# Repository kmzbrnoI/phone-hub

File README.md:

# Telephone distribution system hub

This PCB allows you to use ethernet cables to distribute at most 4 telephone
lines over a single ethernet cable.

It uses standard ethernet pinout.

Created in Eagle 7.2.0 by Jan Horacek in 2015
([jan.horacek@kmz-brno.cz](mailto:jan.horacek@kmz-brno.cz))

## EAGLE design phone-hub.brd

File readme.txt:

Telephone distribution system hub.
This PCB uses ethernet pinout.

Created in Eagle 7.2.0

Copyright:
    2015 Jan Horacek (jan.horacek@kmz-brno.cz)

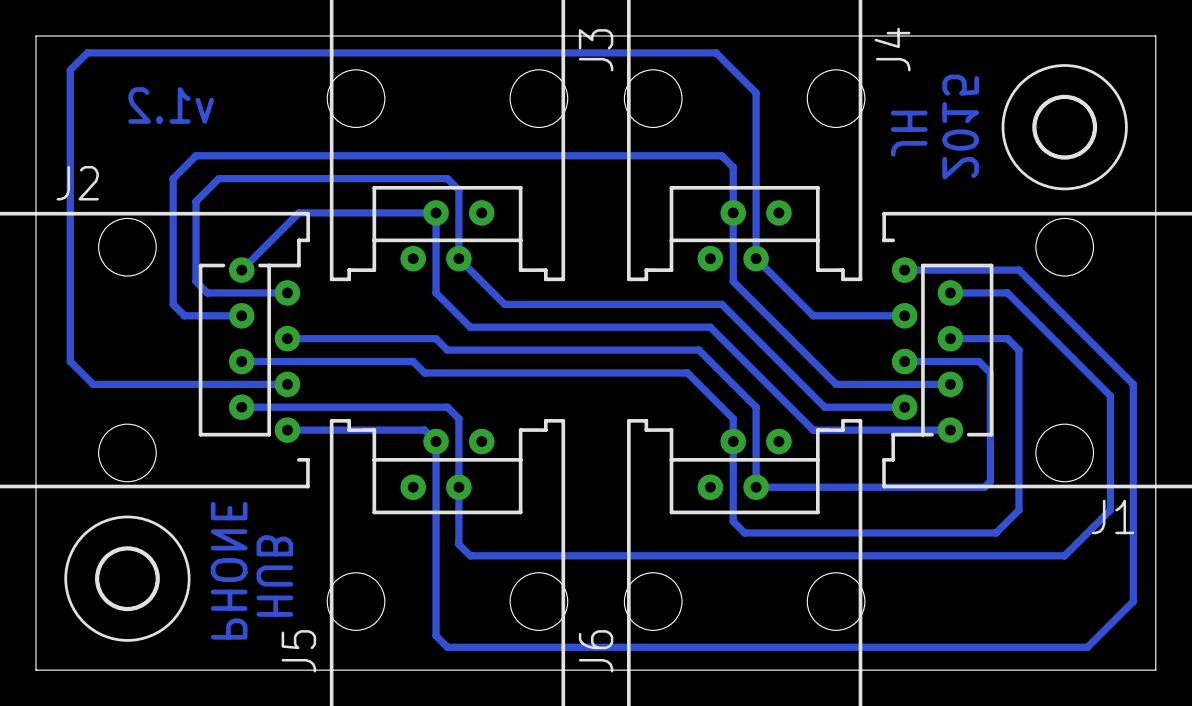
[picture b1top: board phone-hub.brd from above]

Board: 2 copper layers, 62.2 x 35.2 mm, 8 parts (0 on the bottom side), 8 nets.

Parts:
J1, J2: WEBP8-8
J3, J4, J5, J6: WEBP6-4
U$1, U$2: 3,2

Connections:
unnamed: J1.1, J2.1, J3.3
unnamed: J1.2, J2.2, J3.2
unnamed: J1.3, J2.3, J4.3
unnamed: J1.4, J2.4, J6.3
unnamed: J1.6, J2.6, J4.2
unnamed: J1.5, J2.5, J6.2
unnamed: J1.8, J2.8, J5.2
unnamed: J1.7, J2.7, J5.3

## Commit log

2015-05-30 Initial commit.
2015-05-30 Odstraneno eagle.epf
2016-02-12 New Eagle.
2017-08-03 Change README format to markdown.
